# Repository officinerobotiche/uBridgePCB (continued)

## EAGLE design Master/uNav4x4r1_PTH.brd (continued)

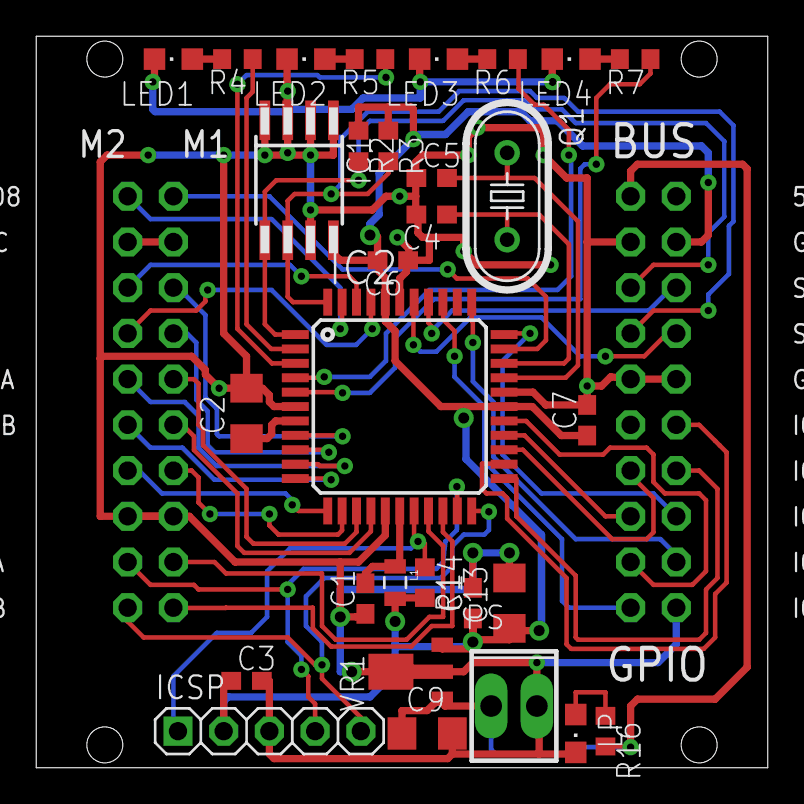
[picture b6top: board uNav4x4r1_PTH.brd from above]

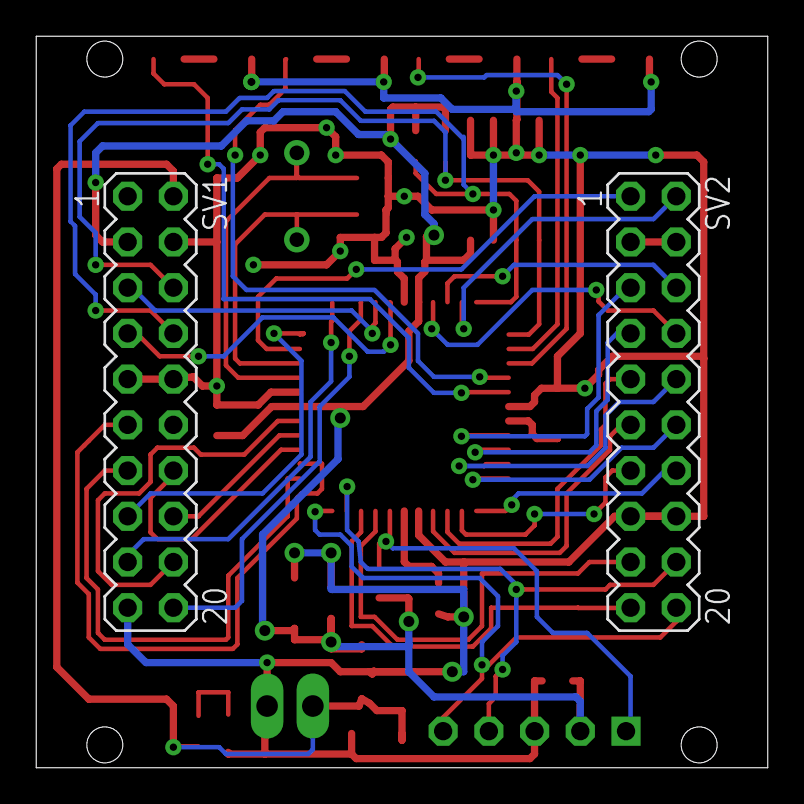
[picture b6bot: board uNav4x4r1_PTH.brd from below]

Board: 2 copper layers, 40.6 x 40.6 mm, 32 parts (2 on the bottom side), 46 nets.

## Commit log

2015-01-13 First commit / temporary repository files / I must organize them
2015-01-22 updated with encoder and temperature connectors
2015-01-22 add SATA connector
2015-01-24 obsolete file removed
2015-01-24 Final release of uBridge
2015-01-26 Final revision
2015-03-24 First version of README.md file
2015-03-24 README update
2015-03-24 little update on README
2015-08-10 Update some signal name and wrong silkscreen on Encoder connector.
2015-08-10 Solved little issue on label name and release file name.
